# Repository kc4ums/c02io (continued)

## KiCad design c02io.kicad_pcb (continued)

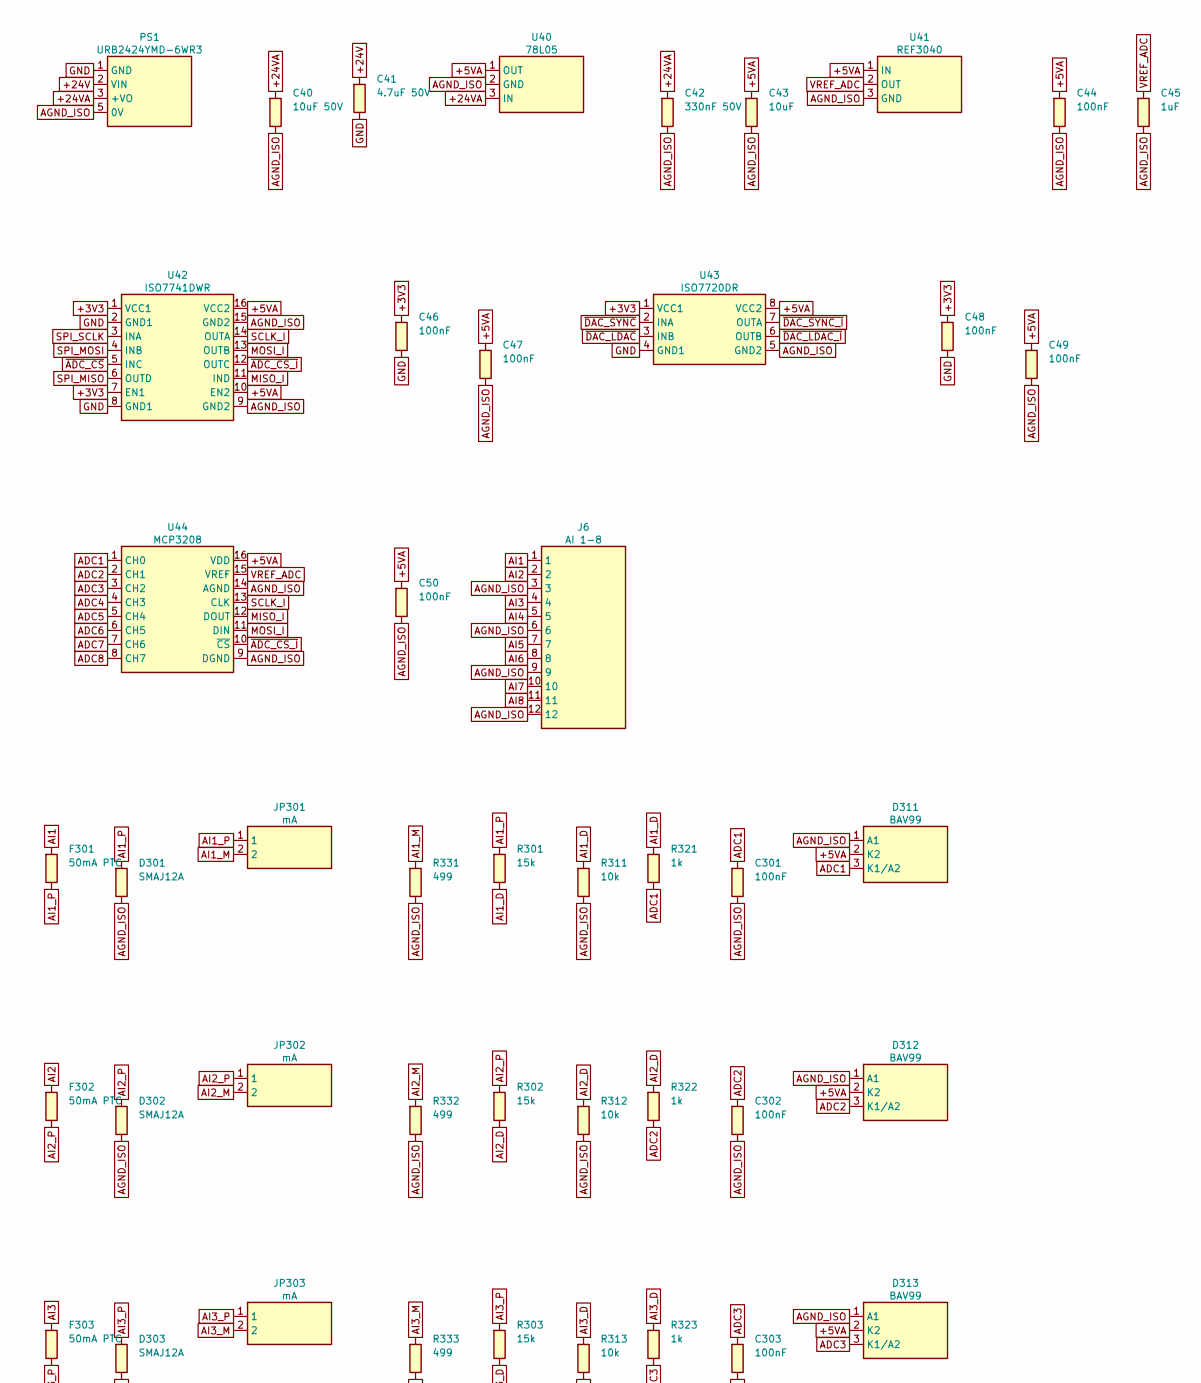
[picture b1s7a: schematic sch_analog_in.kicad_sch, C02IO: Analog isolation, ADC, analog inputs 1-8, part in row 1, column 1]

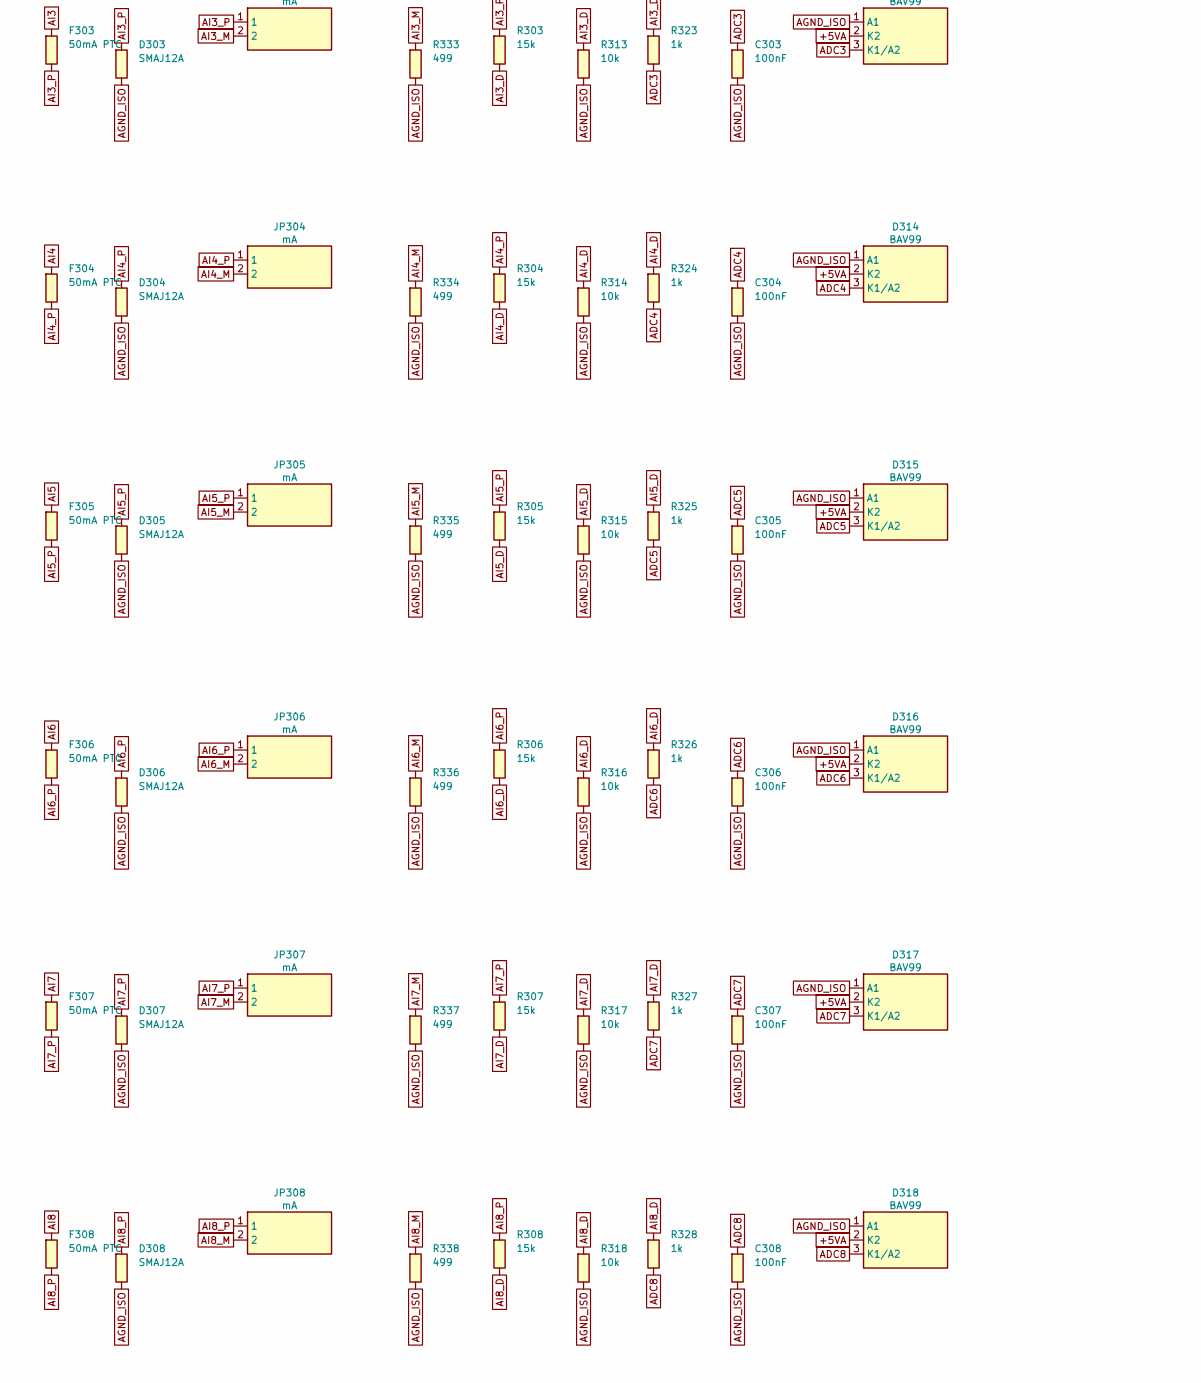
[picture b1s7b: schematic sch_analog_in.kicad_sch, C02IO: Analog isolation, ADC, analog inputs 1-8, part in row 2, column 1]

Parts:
C40: 10uF 50V; C_1210_3225Metric
C41: 4.7uF 50V; C_1210_3225Metric
C42: 330nF 50V; C_0603_1608Metric
C43: 10uF; C_0805_2012Metric
C44, C46, C47, C48, C49, C50, C301, C302, C303, C304, C305, C306, C307, C308: 100nF; C_0603_1608Metric
C45: 1uF; C_0603_1608Metric
D301, D302, D303, D304, D305, D306, D307, D308: SMAJ12A; D_SMA
D311, D312, D313, D314, D315, D316, D317, D318: BAV99; SOT-23; MPN Nexperia BAV99 (3 = common)
F301, F302, F303, F304, F305, F306, F307, F308: 50mA PTC; Fuse_1812_4532Metric
J6: AI 1-8; PhoenixContact_MC_1,5_12-G-3.81_1x12_P3.81mm_Horizontal
JP301, JP302, JP303, JP304, JP305, JP306, JP307, JP308: mA; PinHeader_1x02_P2.54mm_Vertical
PS1: URB2424YMD-6WR3; Mornsun_URB_YMD-6WR3_THT; MPN Mornsun URB2424YMD-6WR3
R301, R302, R303, R304, R305, R306, R307, R308: 15k; R_0603_1608Metric
R311, R312, R313, R314, R315, R316, R317, R318: 10k; R_0603_1608Metric
R321, R322, R323, R324, R325, R326, R327, R328: 1k; R_0603_1608Metric
R331, R332, R333, R334, R335, R336, R337, R338: 499; R_2010_5025Metric
U40: 78L05; SOT-89-3; MPN 78L05 SOT-89 (1 OUT, 2 GND, 3 IN), 30 V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
U41: REF3040; SOT-23; MPN TI REF3040AIDBZR
U42: ISO7741DWR; SOIC-16W_7.5x10.3mm_P1.27mm; MPN TI ISO7741DWR (default high)
U43: ISO7720DR; SOIC-8_3.9x4.9mm_P1.27mm; MPN TI ISO7720DR (default high)
U44: MCP3208; SOIC-16_3.9x9.9mm_P1.27mm; MPN Microchip MCP3208-CI/SL

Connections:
+3V3: C46.1, C48.1, U42.1 (VCC1), U42.7 (EN1), U43.1 (VCC1); also elsewhere on the board
+5VA: C43.1, C44.1, C47.1, C49.1, C50.1, D311.2 (K2), D312.2 (K2), D313.2 (K2), D314.2 (K2), D315.2 (K2), D316.2 (K2), D317.2 (K2), D318.2 (K2), U40.1 (OUT), U41.1 (IN), U42.10 (EN2), U42.16 (VCC2), U43.8 (VCC2), U44.16 (VDD); also elsewhere on the board
+24V: C41.1, PS1.2 (VIN); also elsewhere on the board
+24VA: C40.1, C42.1, PS1.3 (+VO), U40.3 (IN); also elsewhere on the board
ADC1: C301.1, D311.3 (K1/A2), R321.2, U44.1 (CH0)
ADC2: C302.1, D312.3 (K1/A2), R322.2, U44.2 (CH1)
ADC3: C303.1, D313.3 (K1/A2), R323.2, U44.3 (CH2)
ADC4: C304.1, D314.3 (K1/A2), R324.2, U44.4 (CH3)
ADC5: C305.1, D315.3 (K1/A2), R325.2, U44.5 (CH4)
ADC6: C306.1, D316.3 (K1/A2), R326.2, U44.6 (CH5)
ADC7: C307.1, D317.3 (K1/A2), R327.2, U44.7 (CH6)
ADC8: C308.1, D318.3 (K1/A2), R328.2, U44.8 (CH7)
AGND_ISO: C40.2, C42.2, C43.2, C44.2, C45.2, C47.2, C49.2, C50.2, C301.2, C302.2, C303.2, C304.2, C305.2, C306.2, C307.2, C308.2, D301.2 (A), D302.2 (A), D303.2 (A), D304.2 (A), D305.2 (A), D306.2 (A), D307.2 (A), D308.2 (A), D311.1 (A1), D312.1 (A1), D313.1 (A1), D314.1 (A1), D315.1 (A1), D316.1 (A1), D317.1 (A1), D318.1 (A1), J6.3, J6.6, J6.9, J6.12, PS1.5 (0V), R311.2, R312.2, R313.2, R314.2, R315.2, R316.2, R317.2, R318.2, R331.2, R332.2, R333.2, R334.2, R335.2, R336.2, R337.2, R338.2, U40.2 (GND), U41.3 (GND), U42.9 (GND2), U42.15 (GND2), U43.5 (GND2), U44.9 (DGND), U44.14 (AGND); also elsewhere on the board
AI1: F301.1, J6.1
AI1_D: R301.2, R311.1, R321.1
AI1_M: JP301.2, R331.1
AI1_P: D301.1 (K), F301.2, JP301.1, R301.1
AI2: F302.1, J6.2
AI2_D: R302.2, R312.1, R322.1
AI2_M: JP302.2, R332.1
AI2_P: D302.1 (K), F302.2, JP302.1, R302.1
AI3: F303.1, J6.4
AI3_D: R303.2, R313.1, R323.1
AI3_M: JP303.2, R333.1
AI3_P: D303.1 (K), F303.2, JP303.1, R303.1
AI4: F304.1, J6.5
AI4_D: R304.2, R314.1, R324.1
AI4_M: JP304.2, R334.1
AI4_P: D304.1 (K), F304.2, JP304.1, R304.1
AI5: F305.1, J6.7
AI5_D: R305.2, R315.1, R325.1
AI5_M: JP305.2, R335.1
AI5_P: D305.1 (K), F305.2, JP305.1, R305.1
AI6: F306.1, J6.8
AI6_D: R306.2, R316.1, R326.1
AI6_M: JP306.2, R336.1
AI6_P: D306.1 (K), F306.2, JP306.1, R306.1
AI7: F307.1, J6.10
AI7_D: R307.2, R317.1, R327.1
AI7_M: JP307.2, R337.1
AI7_P: D307.1 (K), F307.2, JP307.1, R307.1
AI8: F308.1, J6.11
AI8_D: R308.2, R318.1, R328.1
AI8_M: JP308.2, R338.1
AI8_P: D308.1 (K), F308.2, JP308.1, R308.1
GND: C41.2, C46.2, C48.2, PS1.1 (GND), U42.2 (GND1), U42.8 (GND1), U43.4 (GND1); also elsewhere on the board
MISO_I: U42.11 (IND), U44.12 (DOUT)
MOSI_I: U42.13 (OUTB), U44.11 (DIN); also elsewhere on the board
SCLK_I: U42.14 (OUTA), U44.13 (CLK); also elsewhere on the board
SPI_MISO: U42.6 (OUTD); also elsewhere on the board
SPI_MOSI: U42.4 (INB); also elsewhere on the board
SPI_SCLK: U42.3 (INA); also elsewhere on the board
VREF_ADC: C45.1, U41.2 (OUT), U44.15 (VREF)
~ADC_CS_I: U42.12 (OUTC), U44.10 (~CS)
~ADC_CS: U42.5 (INC); also elsewhere on the board
~DAC_LDAC_I: U43.6 (OUTB); also elsewhere on the board
~DAC_LDAC: U43.3 (INB); also elsewhere on the board
~DAC_SYNC_I: U43.7 (OUTA); also elsewhere on the board
~DAC_SYNC: U43.2 (INA); also elsewhere on the board

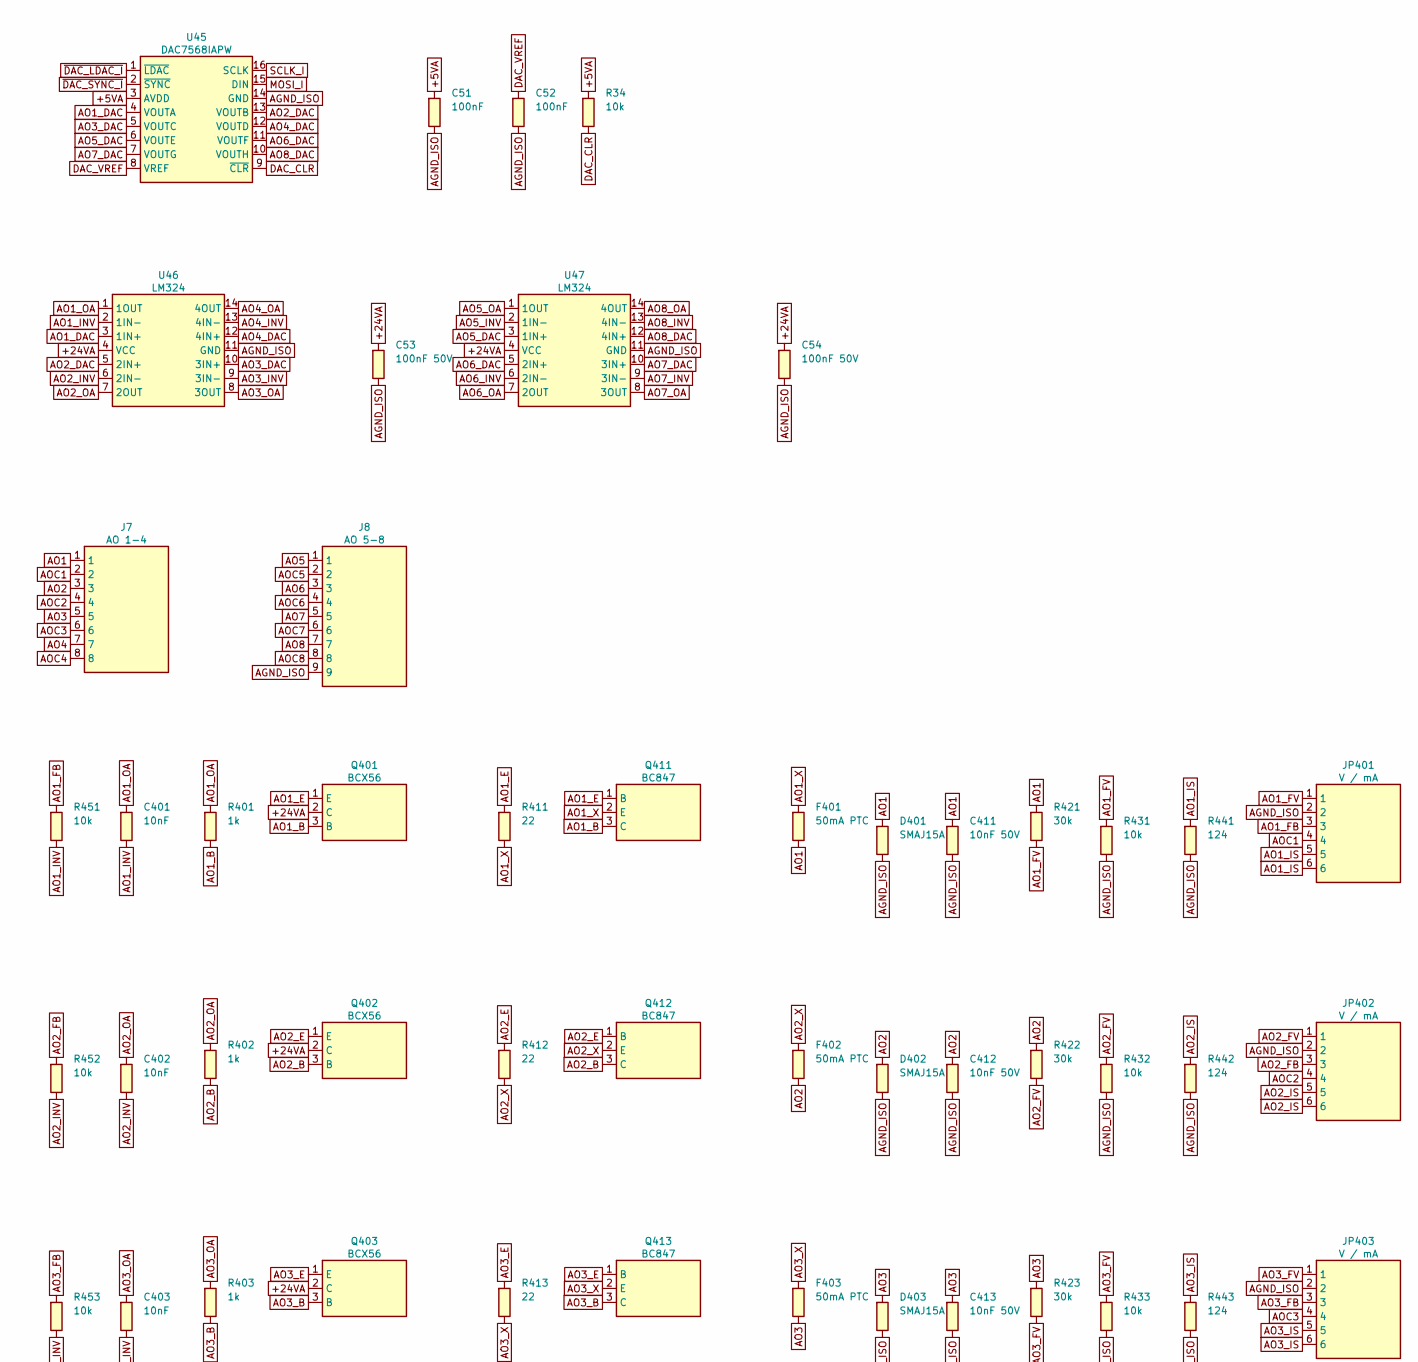
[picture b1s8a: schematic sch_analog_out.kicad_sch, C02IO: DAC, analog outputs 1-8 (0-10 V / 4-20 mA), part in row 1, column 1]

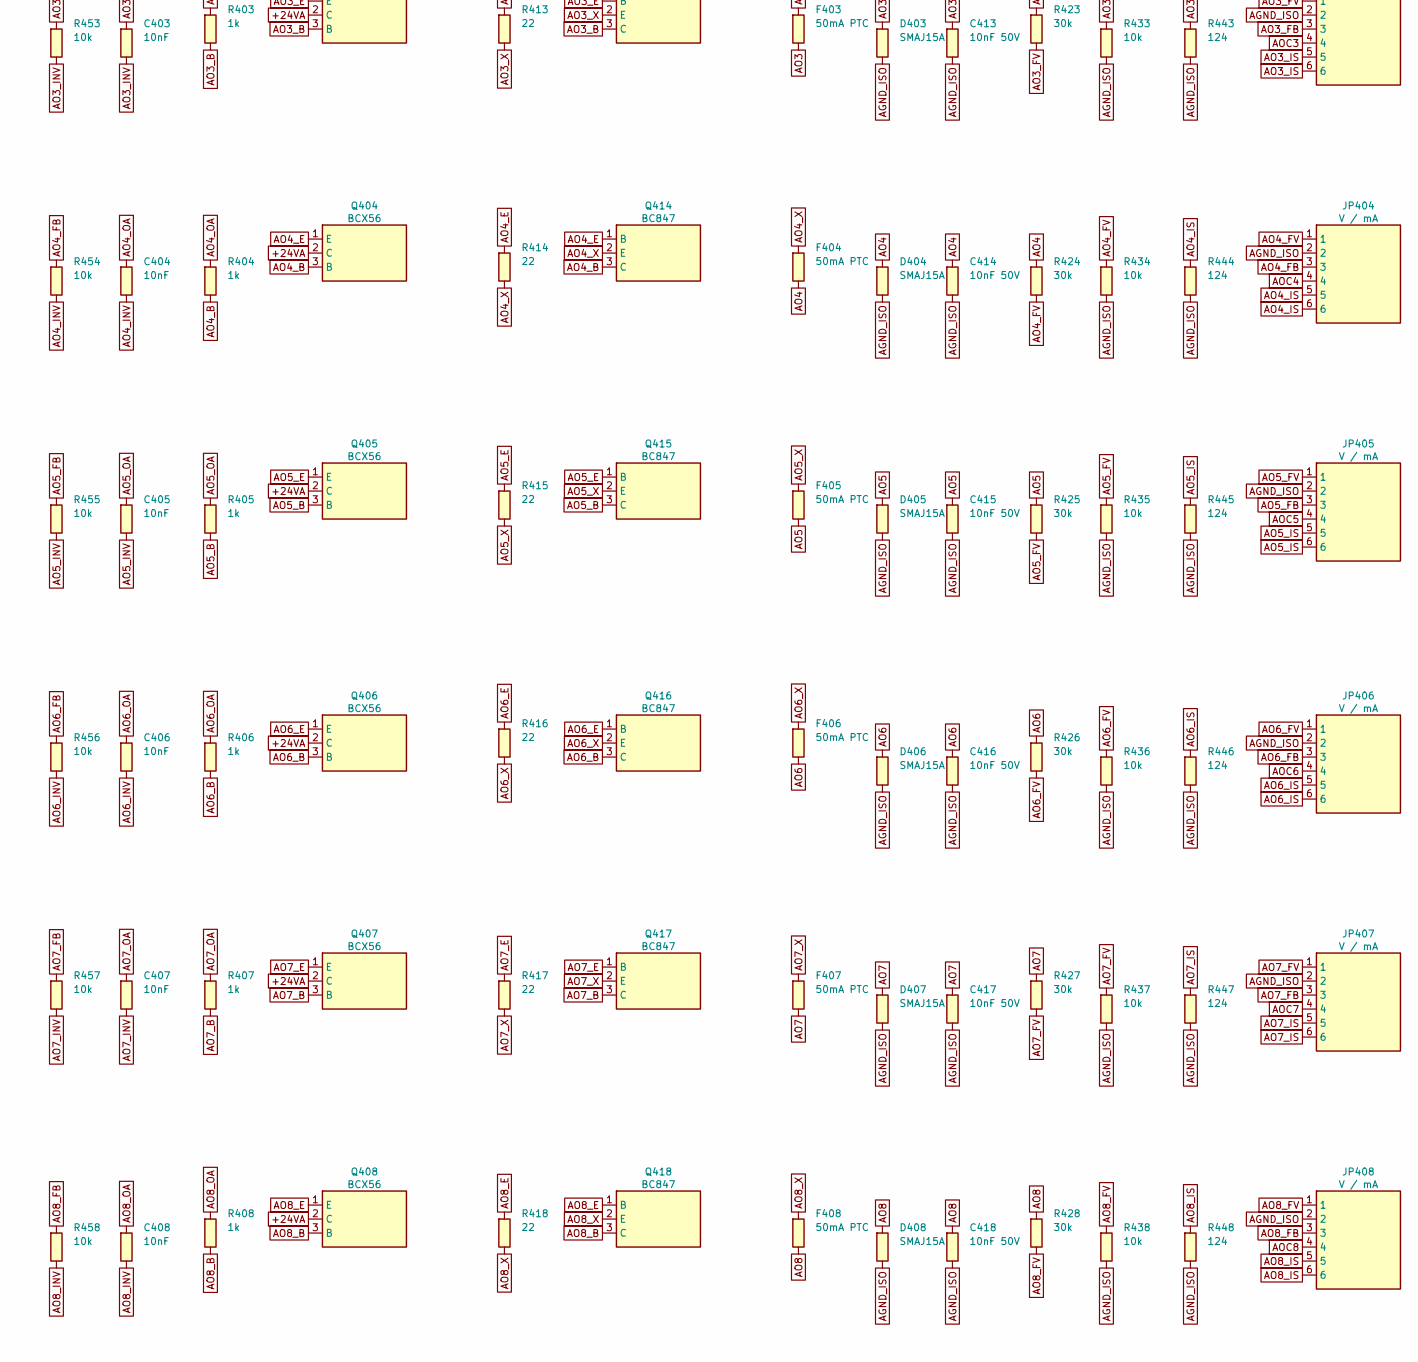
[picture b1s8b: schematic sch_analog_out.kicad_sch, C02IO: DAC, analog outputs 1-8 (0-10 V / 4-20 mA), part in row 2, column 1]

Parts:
C51, C52: 100nF; C_0603_1608Metric
C53, C54: 100nF 50V; C_0603_1608Metric
C401, C402, C403, C404, C405, C406, C407, C408: 10nF; C_0603_1608Metric
C411, C412, C413, C414, C415, C416, C417, C418: 10nF 50V; C_0603_1608Metric
D401, D402, D403, D404, D405, D406, D407, D408: SMAJ15A; D_SMA
F401, F402, F403, F404, F405, F406, F407, F408: 50mA PTC; Fuse_1812_4532Metric
J7: AO 1-4; PhoenixContact_MC_1,5_8-G-3.81_1x08_P3.81mm_Horizontal
J8: AO 5-8; PhoenixContact_MC_1,5_9-G-3.81_1x09_P3.81mm_Horizontal
JP401, JP402, JP403, JP404, JP405, JP406, JP407, JP408: V / mA; PinHeader_2x03_P2.54mm_Vertical
Q401, Q402, Q403, Q404, Q405, Q406, Q407, Q408: BCX56; SOT-89-3; MPN Nexperia BCX56 (1 E, 2 C + tab, 3 B)
Q411, Q412, Q413, Q414, Q415, Q416, Q417, Q418: BC847; SOT-23; MPN Nexperia BC847 (1 B, 2 E, 3 C)
R34, R431, R432, R433, R434, R435, R436, R437, R438, R451, R452, R453, R454, R455, R456, R457, R458: 10k; R_0603_1608Metric
R401, R402, R403, R404, R405, R406, R407, R408: 1k; R_0603_1608Metric
R411, R412, R413, R414, R415, R416, R417, R418: 22; R_0603_1608Metric
R421, R422, R423, R424, R425, R426, R427, R428: 30k; R_0603_1608Metric
R441, R442, R443, R444, R445, R446, R447, R448: 124; R_0805_2012Metric
U45: DAC7568IAPW; TSSOP-16_4.4x5mm_P0.65mm; MPN TI DAC7568IAPWR (A grade)
U46, U47: LM324; SOIC-14_3.9x8.7mm_P1.27mm; MPN TI LM324DR

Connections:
+5VA: C51.1, R34.1, U45.3 (AVDD); also elsewhere on the board
+24VA: C53.1, C54.1, Q401.2 (C), Q402.2 (C), Q403.2 (C), Q404.2 (C), Q405.2 (C), Q406.2 (C), Q407.2 (C), Q408.2 (C), U46.4 (VCC), U47.4 (VCC); also elsewhere on the board
AGND_ISO: C51.2, C52.2, C53.2, C54.2, C411.2, C412.2, C413.2, C414.2, C415.2, C416.2, C417.2, C418.2, D401.2 (A), D402.2 (A), D403.2 (A), D404.2 (A), D405.2 (A), D406.2 (A), D407.2 (A), D408.2 (A), J8.9, JP401.2, JP402.2, JP403.2, JP404.2, JP405.2, JP406.2, JP407.2, JP408.2, R431.2, R432.2, R433.2, R434.2, R435.2, R436.2, R437.2, R438.2, R441.2, R442.2, R443.2, R444.2, R445.2, R446.2, R447.2, R448.2, U45.14 (GND), U46.11 (GND), U47.11 (GND); also elsewhere on the board
AO1: C411.1, D401.1 (K), F401.2, J7.1, R421.1
AO1_B: Q401.3 (B), Q411.3 (C), R401.2
AO1_DAC: U45.4 (VOUTA), U46.3 (1IN+)
AO1_E: Q401.1 (E), Q411.1 (B), R411.1
AO1_FB: JP401.3, R451.1
AO1_FV: JP401.1, R421.2, R431.1
AO1_INV: C401.2, R451.2, U46.2 (1IN-)
AO1_IS: JP401.5, JP401.6, R441.1
AO1_OA: C401.1, R401.1, U46.1 (1OUT)
AO1_X: F401.1, Q411.2 (E), R411.2
AO2: C412.1, D402.1 (K), F402.2, J7.3, R422.1
AO2_B: Q402.3 (B), Q412.3 (C), R402.2
AO2_DAC: U45.13 (VOUTB), U46.5 (2IN+)
AO2_E: Q402.1 (E), Q412.1 (B), R412.1
AO2_FB: JP402.3, R452.1
AO2_FV: JP402.1, R422.2, R432.1
AO2_INV: C402.2, R452.2, U46.6 (2IN-)
AO2_IS: JP402.5, JP402.6, R442.1
AO2_OA: C402.1, R402.1, U46.7 (2OUT)
AO2_X: F402.1, Q412.2 (E), R412.2
AO3: C413.1, D403.1 (K), F403.2, J7.5, R423.1
AO3_B: Q403.3 (B), Q413.3 (C), R403.2
AO3_DAC: U45.5 (VOUTC), U46.10 (3IN+)
AO3_E: Q403.1 (E), Q413.1 (B), R413.1
AO3_FB: JP403.3, R453.1
AO3_FV: JP403.1, R423.2, R433.1
AO3_INV: C403.2, R453.2, U46.9 (3IN-)
AO3_IS: JP403.5, JP403.6, R443.1
AO3_OA: C403.1, R403.1, U46.8 (3OUT)
AO3_X: F403.1, Q413.2 (E), R413.2
AO4: C414.1, D404.1 (K), F404.2, J7.7, R424.1
AO4_B: Q404.3 (B), Q414.3 (C), R404.2
AO4_DAC: U45.12 (VOUTD), U46.12 (4IN+)
AO4_E: Q404.1 (E), Q414.1 (B), R414.1
AO4_FB: JP404.3, R454.1
AO4_FV: JP404.1, R424.2, R434.1
AO4_INV: C404.2, R454.2, U46.13 (4IN-)
AO4_IS: JP404.5, JP404.6, R444.1
AO4_OA: C404.1, R404.1, U46.14 (4OUT)
AO4_X: F404.1, Q414.2 (E), R414.2
AO5: C415.1, D405.1 (K), F405.2, J8.1, R425.1
AO5_B: Q405.3 (B), Q415.3 (C), R405.2
AO5_DAC: U45.6 (VOUTE), U47.3 (1IN+)
AO5_E: Q405.1 (E), Q415.1 (B), R415.1
AO5_FB: JP405.3, R455.1
AO5_FV: JP405.1, R425.2, R435.1
AO5_INV: C405.2, R455.2, U47.2 (1IN-)
AO5_IS: JP405.5, JP405.6, R445.1
AO5_OA: C405.1, R405.1, U47.1 (1OUT)
AO5_X: F405.1, Q415.2 (E), R415.2
AO6: C416.1, D406.1 (K), F406.2, J8.3, R426.1
AO6_B: Q406.3 (B), Q416.3 (C), R406.2
AO6_DAC: U45.11 (VOUTF), U47.5 (2IN+)
AO6_E: Q406.1 (E), Q416.1 (B), R416.1
AO6_FB: JP406.3, R456.1
AO6_FV: JP406.1, R426.2, R436.1
AO6_INV: C406.2, R456.2, U47.6 (2IN-)
AO6_IS: JP406.5, JP406.6, R446.1
AO6_OA: C406.1, R406.1, U47.7 (2OUT)
AO6_X: F406.1, Q416.2 (E), R416.2
AO7: C417.1, D407.1 (K), F407.2, J8.5, R427.1
AO7_B: Q407.3 (B), Q417.3 (C), R407.2
AO7_DAC: U45.7 (VOUTG), U47.10 (3IN+)
AO7_E: Q407.1 (E), Q417.1 (B), R417.1
AO7_FB: JP407.3, R457.1
AO7_FV: JP407.1, R427.2, R437.1
AO7_INV: C407.2, R457.2, U47.9 (3IN-)
AO7_IS: JP407.5, JP407.6, R447.1
AO7_OA: C407.1, R407.1, U47.8 (3OUT)
AO7_X: F407.1, Q417.2 (E), R417.2
AO8: C418.1, D408.1 (K), F408.2, J8.7, R428.1
AO8_B: Q408.3 (B), Q418.3 (C), R408.2
AO8_DAC: U45.10 (VOUTH), U47.12 (4IN+)
AO8_E: Q408.1 (E), Q418.1 (B), R418.1
AO8_FB: JP408.3, R458.1
AO8_FV: JP408.1, R428.2, R438.1
AO8_INV: C408.2, R458.2, U47.13 (4IN-)
AO8_IS: JP408.5, JP408.6, R448.1
AO8_OA: C408.1, R408.1, U47.14 (4OUT)
AO8_X: F408.1, Q418.2 (E), R418.2
AOC1: J7.2, JP401.4
AOC2: J7.4, JP402.4
AOC3: J7.6, JP403.4
AOC4: J7.8, JP404.4
AOC5: J8.2, JP405.4
AOC6: J8.4, JP406.4
AOC7: J8.6, JP407.4
AOC8: J8.8, JP408.4
DAC_CLR: R34.2, U45.9 (~CLR)
DAC_VREF: C52.1, U45.8 (VREF)
MOSI_I: U45.15 (DIN); also elsewhere on the board
SCLK_I: U45.16 (SCLK); also elsewhere on the board
~DAC_LDAC_I: U45.1 (~LDAC); also elsewhere on the board
~DAC_SYNC_I: U45.2 (~SYNC); also elsewhere on the board

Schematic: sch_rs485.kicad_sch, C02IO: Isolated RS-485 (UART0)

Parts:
C60: 4.7uF; C_0805_2012Metric
C61: 10uF; C_0805_2012Metric
C62, C63: 100nF; C_0603_1608Metric
C64: 1uF; C_0603_1608Metric
D7: SM712; SOT-23; MPN Semtech SM712
J9: RS-485; PhoenixContact_MC_1,5_3-G-3.81_1x03_P3.81mm_Horizontal
JP3: TERM; PinHeader_1x02_P2.54mm_Vertical
PS2: B0505XT-1WR3; Mornsun_B05_XT-1WR3_SMD; MPN Mornsun B0505XT-1WR3
R50: 330; R_1206_3216Metric
R51: 10k; R_0603_1608Metric
R52, R53: 680; R_0603_1608Metric
R54: 120; R_1206_3216Metric
U50: CA-IS3082WX; SOIC-16W_7.5x10.3mm_P1.27mm; MPN Chipanalog CA-IS3082WX

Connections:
+3V3: C62.1, R51.1, U50.1 (VDDA); also elsewhere on the board
+5V: C60.1, PS2.2 (VIN); also elsewhere on the board
+5V_485: C61.1, C63.1, C64.1, PS2.5 (+VO), R50.1, R52.1, U50.16 (VDDB)
DIR485: U50.4 (~RE), U50.5 (DE); also elsewhere on the board
GND: C60.2, C62.2, PS2.1 (GND), U50.2 (GNDA), U50.7 (GNDA), U50.8 (GNDA); also elsewhere on the board
GND_485: C61.2, C63.2, C64.2, D7.3 (GND), J9.3, PS2.4 (0V), R50.2, R53.2, U50.9 (GNDB), U50.10 (GNDB), U50.15 (GNDB)
RS485_A: D7.1 (IO1), J9.1, R52.2, R54.1, U50.12 (A)
RS485_B: D7.2 (IO2), J9.2, JP3.2, R53.1, U50.13 (B)
RT_B: JP3.1, R54.2
UA_RX: R51.2, U50.3 (RO); also elsewhere on the board
UA_TX: U50.6 (DI); also elsewhere on the board

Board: 4 copper layers, 494 parts (0 on the bottom side), 365 nets, no tracks yet.

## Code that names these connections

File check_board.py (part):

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check([n for n, s in N.items() if s and n == '+5V'] and
      not any(('U1', str(k)) in N['+3V3'] for k in (77, 79, 81, 83, 85, 87)),
      'CM5 5 V input pins not on 3.3 V')
GPIO_FN = {11: 'SR_SCLK', 10: 'SR_MOSI', 9: 'SR_MISO', 8: 'SR_LATCH',          # SPI0
           21: 'SPI_SCLK', 20: 'SPI_MOSI', 19: 'SPI_MISO', 18: '~{ADC_CS}', 16: '~{DAC_SYNC}',  # SPI1
           14: 'UA_TX', 15: 'UA_RX', 17: 'DIR485'}                            # UART0
check(all(pin('U1', board.CM5_GPIO[g]) == n for g, n in GPIO_FN.items()),
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ETH = {12: 'ETH0_P', 10: 'ETH0_N', 4: 'ETH1_P', 6: 'ETH1_N', 11: 'ETH2_P', 9: 'ETH2_N', 3: 'ETH3_P', 5: 'ETH3_N'}
JACK = {'ETH0_P': 1, 'ETH0_N': 2, 'ETH1_P': 3, 'ETH1_N': 6, 'ETH2_P': 7, 'ETH2_N': 8, 'ETH3_P': 9, 'ETH3_N': 10}
check(all(pin('U1', k) == n and pin('J12', JACK[n]) == n for k, n in ETH.items())
      and pin('J12', 4) == pin('J12', 5) == 'ETH_CT' and two_pin('C70') == ('ETH_CT', 'GND'),
      'Ethernet: CM5 pairs 0-3 to MagJack TRD0-3 as on the CM5 IO board; centre taps to 100 nF')
check(pin('J12', 15) == pin('J12', 17) == '+3V3' and two_pin('R25') == ('ETH_NLED3', 'ETH_LG_K')
      and pin('J12', 18) == 'ETH_LG_K' and two_pin('R26') == ('ETH_NLED2', 'ETH_LY_K') and pin('J12', 16) == 'ETH_LY_K'
      and pin('U1', 15) == 'ETH_NLED3' and pin('U1', 17) == 'ETH_NLED2',
      'Ethernet LEDs: anodes 3.3 V, nLED3 -> green, nLED2 -> yellow through 470R')
check(pin('U1', 103) == 'USB_DN' and pin('U1', 105) == 'USB_DP'
      and pin('J13', 'A6') == pin('J13', 'B6') == 'USB_DP' and pin('J13', 'A7') == pin('J13', 'B7') == 'USB_DN'
      and two_pin('R27') == ('USB_CC1', 'GND') and two_pin('R28') == ('USB_CC2', 'GND')
      and pin('J13', 'A5') == 'USB_CC1' and pin('J13', 'B5') == 'USB_CC2',
      'USB-C: D+/D- both orientations to CM5 USB_P (105) / USB_N (103); Rd 5.1k on CC1, CC2')
check(not set(N['USB_VBUS']) & set(N['+5V']) and sorted(r for r, _ in N['USB_VBUS']) == ['C71', 'J13', 'J13', 'J13', 'J13', 'U51'],
      'USB VBUS reaches only the ESD part and 100 nF (never the board +5V)')
check([pin('U51', k) for k in range(1, 7)] == ['USB_DP', 'GND', 'USB_DN', 'USB_DN', 'USB_VBUS', 'USB_DP'],
      'USBLC6-2SC6: 1/6 D+, 3/4 D-, 2 GND, 5 VBUS')
check(two_pin('JP1') == ('~{RPIBOOT}', 'GND') and pin('U1', 93) == '~{RPIBOOT}'
      and two_pin('SW1') == ('~{PWR_BUT}', 'GND') and pin('U1', 92) == '~{PWR_BUT}',
      'nRPIBOOT jumper (93) and power button (92) to GND')
check(pin('U1', 99) is None and pin('U1', 20) is None and pin('U1', 101) is None and pin('U1', 76) is None,
      'PMIC_Enable, EEPROM_nWP, USB_OTG_ID, VBAT left open')
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# ---------------------------------------------------------------- shift registers
HC165_IN = (11, 12, 13, 14, 3, 4, 5, 6)
HC595_Q = (15, 1, 2, 3, 4, 5, 6, 7)
check(pin('U14', 9) == 'SR_MISO' and pin('U15', 9) == 'SR_CHAIN_I' and pin('U14', 10) == 'SR_CHAIN_I'
      and pin('U15', 10) == 'GND' and all(pin(u, 1) == '~{DI_LOAD}' and pin(u, 2) == 'SR_SCLK'
                                          and pin(u, 15) == 'GND' for u in ('U14', 'U15')),
      '74HC165 chain: U15 QH -> U14 SER, U14 QH -> MISO; /PL = GPIO6, CLK = SCLK, CLK INH low')
check(pin('U16', 14) == 'SR_MOSI' and pin('U16', 9) == 'SR_CHAIN_O' and pin('U17', 14) == 'SR_CHAIN_O'
      and all(pin(u, 11) == 'SR_SCLK' and pin(u, 12) == 'SR_LATCH' and pin(u, 13) == '~{OUT_OE}'
              and pin(u, 10) == '+3V3' for u in ('U16', 'U17')),
      '74HC595 chain: MOSI -> U16 SER, QH\' -> U17 SER; SRCLK = SCLK, RCLK = CE0, /OE from the watchdog, /SRCLR high')
check(pin('U11', 2) == 'WD_KICK' and pin('U11', 1) == 'GND' and pin('U11', 3) == 'OUT_EN'
      and pin('U11', 4) == '~{OUT_OE}', '74HC123: B = kick, /A low, /R = OUT_EN, /Q drives the 595 /OE')
check(pin('U11', 15) == 'WD_RC' and pin('U11', 14) == 'WD_CX' and two_pin('R5') == ('+3V3', 'WD_RC')
      and two_pin('C5') == ('WD_RC', 'WD_CX'), '74HC123: Rx to VCC at RxCx, Cx between Cx and RxCx')
check(two_pin('R7') == ('OUT_EN', 'GND') and two_pin('R6') == ('WD_KICK', 'GND')
      and pin('U1', board.CM5_GPIO[5]) == 'OUT_EN' and pin('U1', board.CM5_GPIO[4]) == 'WD_KICK',
      'OUT_EN (GPIO5) and WD_KICK (GPIO4) pulled low while the CM5 boots')


# outputs on only while OUT_EN is high and the monostable runs (behaviour, HC123 table)
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             and pin(u, 18 - 2 * ch) == '+5V_IO' and pin(u, 17 - 2 * ch) == 'VIN%d' % n
             and two_pin('R%d' % (220 + n)) == ('VIN%d' % n, '0V_IO')
             and pin(vni, VNI_IN[ch]) == 'VIN%d' % n
             and all(pin(vni, k) == o for k in VNI_OUT[ch]) and pin(vni, VNI_ST[ch]) == 'OUT_FLT'
             and two_pin('R%d' % (240 + n)) == (o, 'DO%d_L' % n)
             and two_pin('D%d' % (200 + n)) == ('0V_IO', 'DO%d_L' % n))
    j, jp = ('J4', 'J5')[(n - 1) // 8], bit + 1
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        print('       output %d: chain %s, terminal %s' % (n, chain, pin(j, jp) == o))
check(okdo, '16 outputs: 595 QA..QH -> 330R -> opto -> VNI4140K IN, all 3 OUT pins, STAT, LED')
check(pin('J4', 9) == '24V_IO' and pin('J4', 10) == '0V_IO', 'field supply in on J4 pins 9-10')
check(pin('U35', 1) == 'FLT_A' and pin('U35', 2) == 'OUT_FLT' and pin('U35', 16) == '~{OUT_FLT}'
      and two_pin('R30') == ('+5V_IO', 'FLT_A') and pin('U1', board.CM5_GPIO[22]) == '~{OUT_FLT}',
      'any VNI STAT low -> opto -> GPIO22 low')
check(pin('U35', 3) == 'FPW_A' and pin('U35', 4) == '0V_IO' and pin('U35', 14) == '~{FIELD_OK}'
      and two_pin('R31') == ('24V_IO', 'FPW_A') and pin('U1', board.CM5_GPIO[23]) == '~{FIELD_OK}',
      'field supply present -> opto -> GPIO23 low')

# ---------------------------------------------------------------- analog
check(pin('U42', 3) == 'SPI_SCLK' and pin('U42', 14) == 'SCLK_I' and pin('U42', 4) == 'SPI_MOSI'
      and pin('U42', 13) == 'MOSI_I' and pin('U42', 5) == '~{ADC_CS}' and pin('U42', 12) == '~{ADC_CS_I}'
      and pin('U42', 11) == 'MISO_I' and pin('U42', 6) == 'SPI_MISO'
      and pin('U42', 7) == '+3V3' and pin('U42', 10) == '+5VA',
      'ISO7741: INA-C -> OUTA-C (SCLK, MOSI, ADC /CS), IND -> OUTD (MISO), EN1/EN2 high')
check(pin('U43', 2) == '~{DAC_SYNC}' and pin('U43', 7) == '~{DAC_SYNC_I}' and pin('U43', 3) == '~{DAC_LDAC}'
      and pin('U43', 6) == '~{DAC_LDAC_I}', 'ISO7720: INA -> OUTA (/SYNC), INB -> OUTB (/LDAC)')
check(pin('U44', 10) == '~{ADC_CS_I}' and pin('U44', 11) == 'MOSI_I' and pin('U44', 12) == 'MISO_I'
      and pin('U44', 13) == 'SCLK_I' and pin('U44', 15) == 'VREF_ADC' and pin('U41', 2) == 'VREF_ADC',
      'MCP3208: /CS, DIN, DOUT, CLK, VREF from the REF3040')
check(pin('U45', 2) == '~{DAC_SYNC_I}' and pin('U45', 1) == '~{DAC_LDAC_I}' and pin('U45', 15) == 'MOSI_I'
      and pin('U45', 16) == 'SCLK_I' and pin('U45', 9) == 'DAC_CLR' and two_pin('R34') == ('+5VA', 'DAC_CLR'),
      'DAC7568: /SYNC, /LDAC, DIN, SCLK; /CLR held high')
DAC_OUT = {1: 4, 2: 13, 3: 5, 4: 12, 5: 6, 6: 11, 7: 7, 8: 10}
okai = True
for n in range(1, 9):
    p = 'AI%d' % n
    c = (two_pin('F%d' % (300 + n)) == (p, p + '_P')
         and two_pin('D%d' % (300 + n)) == (p + '_P', 'AGND_ISO')
         and two_pin('JP%d' % (300 + n)) == (p + '_P', p + '_M')
         and two_pin('R%d' % (330 + n)) == (p + '_M', 'AGND_ISO') and P['R%d' % (330 + n)]['value'] == '499'
         and two_pin('R%d' % (300 + n)) == (p + '_P', p + '_D') and P['R%d' % (300 + n)]['value'] == '15k'
         and two_pin('R%d' % (310 + n)) == (p + '_D', 'AGND_ISO') and P['R%d' % (310 + n)]['value'] == '10k'
         and two_pin('R%d' % (320 + n)) == (p + '_D', 'ADC%d' % n)
         and two_pin('C%d' % (300 + n)) == ('ADC%d' % n, 'AGND_ISO')
         and [pin('D%d' % (310 + n), k) for k in (1, 2, 3)] == ['AGND_ISO', '+5VA', 'ADC%d' % n]
         and pin('U44', n) == 'ADC%d' % n)
    if not c:
        okai = False
        print('       analog input %d wrong' % n)
check(okai, '8 analog inputs: PTC, TVS, mA jumper + 499R, 15k/10k, 1k, 100 nF, BAV99 (3 = common), CHn-1')
check([pin('J6', k) for k in range(1, 13)] == ['AI1', 'AI2', 'AGND_ISO', 'AI3', 'AI4', 'AGND_ISO',
                                               'AI5', 'AI6', 'AGND_ISO', 'AI7', 'AI8', 'AGND_ISO'],
      'analog input terminal J6')
okao = True
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         and two_pin('R%d' % (410 + n)) == (p + 'E', p + 'X')
         and [pin('Q%d' % (410 + n), k) for k in (1, 2, 3)] == [p + 'E', p + 'X', p + 'B']
         and two_pin('F%d' % (400 + n)) == (p + 'X', 'AO%d' % n)
         and two_pin('D%d' % (400 + n)) == ('AO%d' % n, 'AGND_ISO')
         and two_pin('R%d' % (420 + n)) == ('AO%d' % n, p + 'FV')
         and two_pin('R%d' % (430 + n)) == (p + 'FV', 'AGND_ISO')
         and two_pin('R%d' % (440 + n)) == (p + 'IS', 'AGND_ISO')
         and two_pin('R%d' % (450 + n)) == (p + 'FB', p + 'INV')
         and two_pin('C%d' % (400 + n)) == (p + 'OA', p + 'INV')
         and [pin('JP%d' % (400 + n), k) for k in range(1, 7)]
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# gains: V mode 2.5 V * (1 + 30k/10k) = 10 V; mA mode 2.5 V / 124 R
check(P['R421']['value'] == '30k' and P['R431']['value'] == '10k' and P['R441']['value'] == '124',
      'V mode: 0-2.5 V x 4 = 0-10 V; mA mode: 2.5 V / 124 R = 20.2 mA full scale')
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
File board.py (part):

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Rev B: the W65C02S system (CPU, RAM, flash, VIA, UART, decoding) is replaced
by a Raspberry Pi Compute Module 5 with gigabit Ethernet and a USB-C port
(rpiboot flashing). The I/O is unchanged except at its logic end:
    inputs 1-16    2 x 74HC165 on SPI0, loaded by GPIO6
    outputs 1-16   2 x 74HC595 on SPI0, latched by CE0 (GPIO8); /OE from the
                   watchdog (GPIO5 = enable, GPIO4 = kick)
    analog         SPI1 through the ISO7741 / ISO7720 (ADC CE0, DAC CE2, /LDAC GPIO24)
    RS-485         UART0 (GPIO14/15), driver enable on RTS (GPIO17)
    status         /OUT_FLT GPIO22, /FIELD_OK GPIO23, LEDs GPIO12/13
The logic side runs at 3.3 V from the CM5's own 3.3 V output, so nothing
drives a CM5 pin while it is unpowered.

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#   4 watchdog kick, 5 output enable, 6 input load (/PL), 12 RUN LED, 13 FAULT LED,
#   22 /OUT_FLT in, 23 /FIELD_OK in, 24 DAC /LDAC
#   2/3 (I2C1, 1.8k pull-ups on the module), 7, 25, 26, 27 to the expansion header
GPIO_USE = {2: 'GPIO2_SDA', 3: 'GPIO3_SCL', 4: 'WD_KICK', 5: 'OUT_EN', 6: '~{DI_LOAD}',
            7: 'GPIO7', 8: 'SR_LATCH', 9: 'SR_MISO', 10: 'SR_MOSI', 11: 'SR_SCLK',
            12: 'LED_RUN', 13: 'LED_FAULT', 14: 'UA_TX', 15: 'UA_RX', 16: '~{DAC_SYNC}',
            17: 'DIR485', 18: '~{ADC_CS}', 19: 'SPI_MISO', 20: 'SPI_MOSI', 21: 'SPI_SCLK',
            22: '~{OUT_FLT}', 23: '~{FIELD_OK}', 24: '~{DAC_LDAC}', 25: 'GPIO25', 26: 'GPIO26',
            27: 'GPIO27'}
CM5_PINS = {k: None for k in range(1, 201)}
CM5_PINS.update({k: 'GND' for k in CM5_GND})
CM5_PINS.update({k: '+5V' for k in (77, 79, 81, 83, 85, 87)})       # 5 V in, 4.75-5.25 V
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    note='footprint pads 1 and 2 each appear twice')
two('D8', 'ACT', 'LED', 0, 0, 'ACT_K', '+3V3', mpn='0805 LED, green')
two('R24', '1k', 'R', 0, 0, 'ACT_K', 'LED_NACT', note='CM5 activity LED (open drain)')
two('R29', '10k', 'R', 0, 0, 'DIR485', 'GND', note='RS-485 driver off while GPIO17 floats')

# Expansion header (3.3 V logic): I2C1 and four spare GPIOs
part('J11', 'EXPANSION', 'H2x5', 0, 0, pins={
    1: '+3V3', 2: '+5V', 3: 'GPIO2_SDA', 4: 'GND', 5: 'GPIO3_SCL', 6: 'GPIO25', 7: 'GPIO26',
    8: 'GPIO27', 9: 'GND', 10: 'GPIO7'}, note='3V3 5V SDA GND SCL 25 26 27 GND 7')

# ============================================================ watchdog
# CD74HC123 half 1 at 3.3 V: B (rising edge, /A low) retriggers from GPIO4.
# /R = OUT_EN (GPIO5): while it is low, /Q is high and the 74HC595 outputs are
# off. /Q low (= triggered) enables them, so the outputs work only while
# software sets OUT_EN AND keeps kicking. GPIO4 is pulled low so the release of
# /R can't trigger it. tW = 0.45 * Rx * Cx = 0.45 * 100k * 2.2uF = ~100 ms
# (less with the capacitor's DC-bias loss: kick it at least every 25 ms).
# Half 2 unused: /A high, B low, /R low.
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decouple('C14', 0, 0, '+3V3')
two('R5', '100k', 'R', 0, 0, '+3V3', 'WD_RC', note='watchdog Rx')
two('C5', '2.2uF', 'C1206', 0, 0, 'WD_RC', 'WD_CX', note='watchdog Cx, X7R 25 V')
two('R6', '10k', 'R', 0, 0, 'WD_KICK', 'GND', note='GPIO4 low while the CM5 boots')
two('R7', '10k', 'R', 0, 0, 'OUT_EN', 'GND', note='GPIO5 low: outputs off until software sets it')

# SPI chip selects held inactive while the GPIOs are inputs
two('R15', '10k', 'R', 0, 0, '+3V3', '~{ADC_CS}')
two('R16', '10k', 'R', 0, 0, '+3V3', '~{DAC_SYNC}')
two('R17', '10k', 'R', 0, 0, '+3V3', '~{DAC_LDAC}')

# RUN / FAULT LEDs on GPIO12 / GPIO13 (lit when high), power LED on +5V
for i, (net, col) in enumerate((('LED_RUN', 'green'), ('LED_FAULT', 'red'))):
    two('D%d' % (3 + i), 'RUN' if i == 0 else 'FAULT', 'LED', 0, 0,
        'NL%d' % i, net, mpn='0805 LED, ' + col)
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
# 74HC165 x2 (TI SCLS116H): 1 SH/LD, 2 CLK, 3-6 E-H, 7 /QH, 8 GND, 9 QH,
# 10 SER, 11-14 A-D, 15 CLK INH, 16 VCC. Input n -> A..H of U14 (1-8) / U15 (9-16).
# GPIO6 pulses /PL low to load, then SPI0 clocks the chain: U14 QH -> MISO,
# U15 QH -> U14 SER. First bit read = input 8, then 7 .. 1, 16 .. 9 (low = on).
HC165_IN = (11, 12, 13, 14, 3, 4, 5, 6)                  # A..H
for i, (ref, ser, qh) in enumerate((('U14', 'SR_CHAIN_I', 'SR_MISO'), ('U15', 'GND', 'SR_CHAIN_I'))):
    pins = {1: '~{DI_LOAD}', 2: 'SR_SCLK', 7: None, 8: 'GND', 9: qh, 10: ser, 15: 'GND', 16: '+3V3'}
    for k in range(8):
        pins[HC165_IN[k]] = 'DIN%d' % (8 * i + k + 1)
    part(ref, '74HC165', 'SO16', 20 + 40 * i, 50, pins=pins, mpn='Nexperia 74HC165D (LCSC C5613)')
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# U16 (1-8) / U17 (9-16): send outputs 16 .. 9, then 8 .. 1 (MSB first).
HC595_Q = (15, 1, 2, 3, 4, 5, 6, 7)                      # QA..QH
for i, (ref, ser, qh2) in enumerate((('U16', 'SR_MOSI', 'SR_CHAIN_O'), ('U17', 'SR_CHAIN_O', None))):
    pins = {8: 'GND', 9: qh2, 10: '+3V3', 11: 'SR_SCLK', 12: 'SR_LATCH', 13: '~{OUT_OE}',
            14: ser, 16: '+3V3'}
    for k in range(8):
        pins[HC595_Q[k]] = 'DQ%d' % (8 * i + k + 1)
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two('C35', '100nF 50V', 'C', 92, 20, '24V_IO', '0V_IO')
two('C36', '1uF', 'C', 92, 22, '+5V_IO', '0V_IO')

# U35 TLP291-4: ch1 = output fault (GPIO22), ch2 = field power present (GPIO23), ch3-4 spare.
# Fault: +5V_IO -> 2.2k -> opto LED -> OUT_FLT (pulled low by any STATn).
# Field power: 24V_IO -> 10k -> opto LED -> 0V_IO.
opto4('U35', 96, 32, [('FLT_A', 'OUT_FLT', '~{OUT_FLT}', 'GND'),
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                      ('0V_IO', '0V_IO', None, 'GND')])
two('R30', '2.2k', 'R', 92, 28, '+5V_IO', 'FLT_A', note='~1.5 mA; STAT is specified at 1.6 mA')
two('R31', '10k', 'R1206', 92, 30, '24V_IO', 'FPW_A', note='~2.2 mA at 24 V')
two('R32', '22k', 'R', 100, 44, '+3V3', '~{OUT_FLT}', note='GPIO22 pull-up')
two('R33', '22k', 'R', 102, 44, '+3V3', '~{FIELD_OK}', note='GPIO23 pull-up')

# Field terminals (3.81 mm pluggable, top edge)
part('J2', 'DI 1-8', 'TB10', 10, 3, pins={**{i + 1: DI[i] for i in range(8)}, 9: '24V_SNS', 10: '0V_IO'}, note='IN1-IN8, 24V (sensor supply), 0V')
part('J3', 'DI 9-16', 'TB10', 50, 3, pins={**{i + 1: DI[8 + i] for i in range(8)}, 9: '24V_SNS', 10: '0V_IO'}, note='IN9-IN16, 24V (sensor supply), 0V')
part('J4', 'DO 1-8', 'TB10', 120, 3, pins={**{i + 1: 'OUT%d' % (i + 1) for i in range(8)}, 9: '24V_IO', 10: '0V_IO'},
     note='OUT1-OUT8, 24V_IO in, 0V_IO in')
part('J5', 'DO 9-16', 'TB10', 160, 3, pins={**{i + 1: 'OUT%d' % (9 + i) for i in range(8)}, 9: '0V_IO', 10: '0V_IO'}, note='OUT9-OUT16, 0V, 0V (load return)')

# ============================================================ analog isolation
# URB2424YMD-6WR3 (through-hole, 25.4 mm square): 1 GND, 2 Vin, 3 +Vo,
# 4 absent, 5 0V. 1500 VDC isolation, no minimum load.
part('PS1', 'URB2424YMD-6WR3', 'URB', 14, 96, pins={1: 'GND', 2: '+24V', 3: '+24VA', 5: 'AGND_ISO'},
     mpn='Mornsun URB2424YMD-6WR3', note='Cin 100 uF (C1), Cout 10 uF')
two('C40', '10uF 50V', 'C1210', 30, 90, '+24VA', 'AGND_ISO', note='URB output, X7R')
two('C41', '4.7uF 50V', 'C1210', 4, 90, '+24V', 'GND', note='URB input, at the module')
part('U40', '78L05', 'SOT89', 30, 96, pins={1: '+5VA', 2: 'AGND_ISO', 3: '+24VA'},
     mpn='78L05 SOT-89 (1 OUT, 2 GND, 3 IN), 30 V input')
two('C42', '330nF 50V', 'C', 34, 96, '+24VA', 'AGND_ISO')
two('C43', '10uF', 'C0805', 34, 100, '+5VA', 'AGND_ISO')
# REF3040: 1 IN, 2 OUT, 3 GND. 4.096 V for the MCP3208.
part('U41', 'REF3040', 'SOT23', 40, 100, pins={1: '+5VA', 2: 'VREF_ADC', 3: 'AGND_ISO'},
     mpn='TI REF3040AIDBZR')
two('C44', '100nF', 'C', 40, 96, '+5VA', 'AGND_ISO')
two('C45', '1uF', 'C', 44, 100, 'VREF_ADC', 'AGND_ISO', note='ADC reference bypass')
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    two('R%d' % (310 + n), '10k', 'R', x, 98, p + '_D', 'AGND_ISO', note='0.1 %')
    two('R%d' % (320 + n), '1k', 'R', x, 96, p + '_D', 'ADC%d' % n)
    two('C%d' % (300 + n), '100nF', 'C', x, 94, 'ADC%d' % n, 'AGND_ISO')
    part('D%d' % (310 + n), 'BAV99', 'SOT23', x, 90, pins={1: 'AGND_ISO', 2: '+5VA', 3: 'ADC%d' % n},
         mpn='Nexperia BAV99 (3 = common)')

# ============================================================ analog outputs (x8)
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# LM324 x2 on +24VA. Amp k: (out, in-, in+) = 1:(1,2,3) 2:(7,6,5) 3:(8,9,10) 4:(14,13,12)
AMP = {1: (1, 2, 3), 2: (7, 6, 5), 3: (8, 9, 10), 4: (14, 13, 12)}
for i, ref in enumerate(('U46', 'U47')):
    pins = {4: '+24VA', 11: 'AGND_ISO'}
    for k in range(1, 5):
        ch = 4 * i + k
        o, m, pl = AMP[k]
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two('R53', '680', 'R', 186, 108, 'RS485_B', 'GND_485', note='bias')
two('R54', '120', 'R1206', 190, 106, 'RS485_A', 'RT_B', note='termination')
two('JP3', 'TERM', 'H1x2', 194, 106, 'RT_B', 'RS485_B', note='fit at the ends of the bus')
part('D7', 'SM712', 'SOT23', 186, 112, pins={1: 'RS485_A', 2: 'RS485_B', 3: 'GND_485'},
     mpn='Semtech SM712')
part('J9', 'RS-485', 'TB3', 190, 117, pins={1: 'RS485_A', 2: 'RS485_B', 3: 'GND_485'},
     note='A, B, 0V')

# ============================================================ mounting holes
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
